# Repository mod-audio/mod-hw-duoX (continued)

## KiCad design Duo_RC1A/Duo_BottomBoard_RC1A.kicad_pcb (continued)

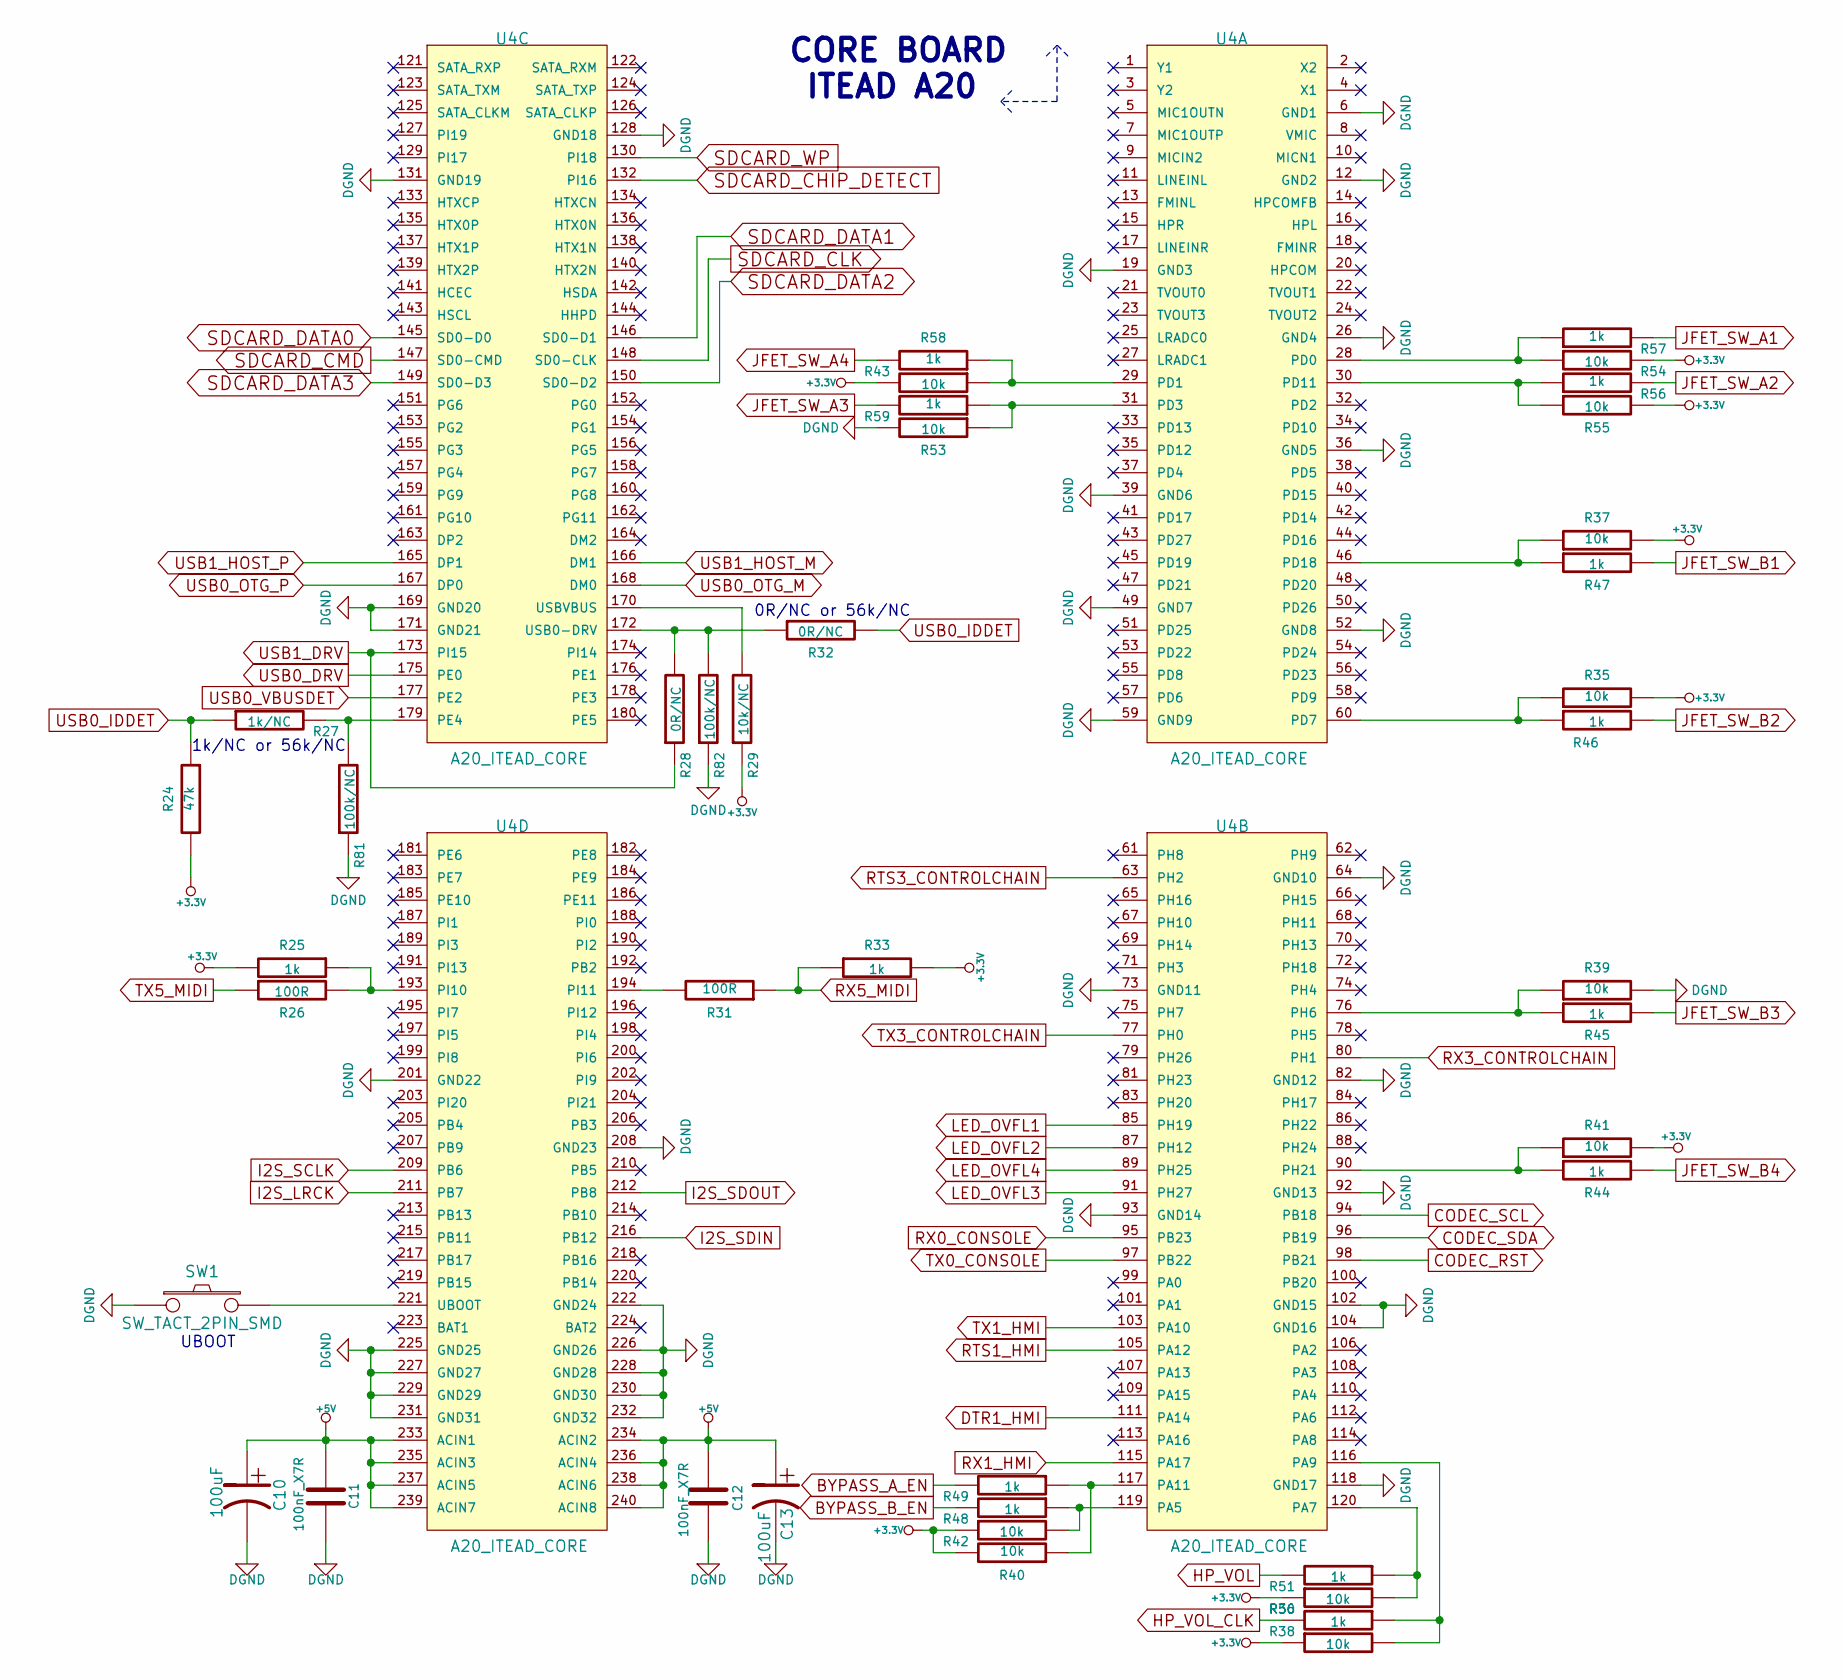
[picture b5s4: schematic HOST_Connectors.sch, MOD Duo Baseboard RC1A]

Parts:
C10, C13: 100uF; Capacitor5x11RM2
C11, C12: 100nF_X7R; SM0603
R24: 47k; SM0603
R25, R33, R44, R45, R46, R47, R48, R49, R50, R51, R56, R57, R58, R59: 1k; SM0603
R26, R31: 100R; SM0603
R27: 1k/NC; SM0603
R28, R32: 0R/NC; SM0603
R29: 10k/NC; SM0603
R35, R36, R37, R38, R39, R40, R41, R42, R43, R53, R54, R55: 10k; SM0603
R81, R82: 100k/NC; SM0603
SW1: SW_TACT_2PIN_SMD; SWITCH_SMD_FSMSM
U4: A20_ITEAD_CORE; A20_ITEAD

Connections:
+3.3V: R24.2, R25.2, R29.1, R33.2, R35.2, R36.1, R37.2, R38.1, R40.2, R41.2, R42.1, R43.2, R54.2, R55.2; also elsewhere on the board
+5V: C10.1, C11.1, C12.2, C13.1, U4.233 (ACIN1), U4.234 (ACIN2), U4.235 (ACIN3), U4.236 (ACIN4), U4.237 (ACIN5), U4.238 (ACIN6), U4.239 (ACIN7), U4.240 (ACIN8); also elsewhere on the board
BYPASS_A_EN: R49.2; also elsewhere on the board
BYPASS_B_EN: R48.2; also elsewhere on the board
CODEC_RST: U4.98 (PB21); also elsewhere on the board
CODEC_SCL: U4.94 (PB18); also elsewhere on the board
CODEC_SDA: U4.96 (PB19); also elsewhere on the board
DGND: C10.2, C11.2, C12.1, C13.2, R39.2, R53.2, R81.1, R82.1, SW1.1, U4.6 (GND1), U4.12 (GND2), U4.19 (GND3), U4.26 (GND4), U4.36 (GND5), U4.39 (GND6), U4.49 (GND7), U4.52 (GND8), U4.59 (GND9), U4.64 (GND10), U4.73 (GND11), U4.82 (GND12), U4.92 (GND13), U4.93 (GND14), U4.102 (GND15), U4.104 (GND16), U4.118 (GND17), U4.128 (GND18), U4.131 (GND19), U4.169 (GND20), U4.171 (GND21), U4.201 (GND22), U4.208 (GND23), U4.222 (GND24), U4.225 (GND25), U4.226 (GND26), U4.227 (GND27), U4.228 (GND28), U4.229 (GND29), U4.230 (GND30), U4.231 (GND31), U4.232 (GND32); also elsewhere on the board
DTR1_HMI: U4.111 (PA14); also elsewhere on the board
HP_VOL: R51.2; also elsewhere on the board
HP_VOL_CLK: R50.2; also elsewhere on the board
I2S_LRCK: U4.211 (PB7); also elsewhere on the board
I2S_SCLK: U4.209 (PB6); also elsewhere on the board
I2S_SDIN: U4.216 (PB12); also elsewhere on the board
I2S_SDOUT: U4.212 (PB8); also elsewhere on the board
JFET_SW_A1: R57.2; also elsewhere on the board
JFET_SW_A2: R56.2; also elsewhere on the board
JFET_SW_A3: R59.2; also elsewhere on the board
JFET_SW_A4: R58.2; also elsewhere on the board
JFET_SW_B1: R47.2; also elsewhere on the board
JFET_SW_B2: R46.2; also elsewhere on the board
JFET_SW_B3: R45.2; also elsewhere on the board
JFET_SW_B4: R44.2; also elsewhere on the board
LED_OVFL1: U4.85 (PH19); also elsewhere on the board
LED_OVFL2: U4.87 (PH12); also elsewhere on the board
LED_OVFL3: U4.91 (PH27); also elsewhere on the board
LED_OVFL4: U4.89 (PH25); also elsewhere on the board
unnamed: R25.1, R26.2, U4.193 (PI10)
unnamed: R27.2, R81.2, U4.179 (PE4)
unnamed: R28.2, R32.1, R82.2, U4.172 (USB0-DRV)
unnamed: R29.2, U4.170 (USBVBUS)
unnamed: R31.2, U4.194 (PI11)
unnamed: R35.1, R46.1, U4.60 (PD7)
unnamed: R36.2, R51.1, U4.120 (PA7)
unnamed: R37.1, R47.1, U4.46 (PD18)
unnamed: R38.2, R50.1, U4.116 (PA9)
unnamed: R39.1, R45.1, U4.76 (PH6)
unnamed: R40.1, R49.1, U4.117 (PA11)
unnamed: R41.1, R44.1, U4.90 (PH21)
unnamed: R42.2, R48.1, U4.119 (PA5)
unnamed: R43.1, R58.1, U4.29 (PD1)
unnamed: R53.1, R59.1, U4.31 (PD3)
unnamed: R54.1, R57.1, U4.28 (PD0)
unnamed: R55.1, R56.1, U4.30 (PD11)
unnamed: SW1.2, U4.221 (UBOOT)
RTS1_HMI: U4.105 (PA12); also elsewhere on the board
RTS3_CONTROLCHAIN: U4.63 (PH2); also elsewhere on the board
RX0_CONSOLE: U4.95 (PB23); also elsewhere on the board
RX1_HMI: U4.115 (PA17); also elsewhere on the board
RX3_CONTROLCHAIN: U4.80 (PH1); also elsewhere on the board
RX5_MIDI: R31.1, R33.1; also elsewhere on the board
SDCARD_CHIP_DETECT: U4.132 (PI16); also elsewhere on the board
SDCARD_CLK: U4.148 (SD0-CLK); also elsewhere on the board
SDCARD_CMD: U4.147 (SD0-CMD); also elsewhere on the board
SDCARD_DATA0: U4.145 (SD0-D0); also elsewhere on the board
SDCARD_DATA1: U4.146 (SD0-D1); also elsewhere on the board
SDCARD_DATA2: U4.150 (SD0-D2); also elsewhere on the board
SDCARD_DATA3: U4.149 (SD0-D3); also elsewhere on the board
SDCARD_WP: U4.130 (PI18); also elsewhere on the board
TX0_CONSOLE: U4.97 (PB22); also elsewhere on the board
TX1_HMI: U4.103 (PA10); also elsewhere on the board
TX3_CONTROLCHAIN: U4.77 (PH0); also elsewhere on the board
TX5_MIDI: R26.1; also elsewhere on the board
USB0_DRV: U4.175 (PE0); also elsewhere on the board
USB0_IDDET: R24.1, R27.1, R32.2; also elsewhere on the board
USB0_OTG_M: U4.168 (DM0); also elsewhere on the board
USB0_OTG_P: U4.167 (DP0); also elsewhere on the board
USB0_VBUSDET: U4.177 (PE2); also elsewhere on the board
USB1_DRV: R28.1, U4.173 (PI15); also elsewhere on the board
USB1_HOST_M: U4.166 (DM1); also elsewhere on the board
USB1_HOST_P: U4.165 (DP1); also elsewhere on the board

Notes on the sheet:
CORE BOARD ITEAD A20
UBOOT
0R/NC or 56k/NC
1k/NC or 56k/NC

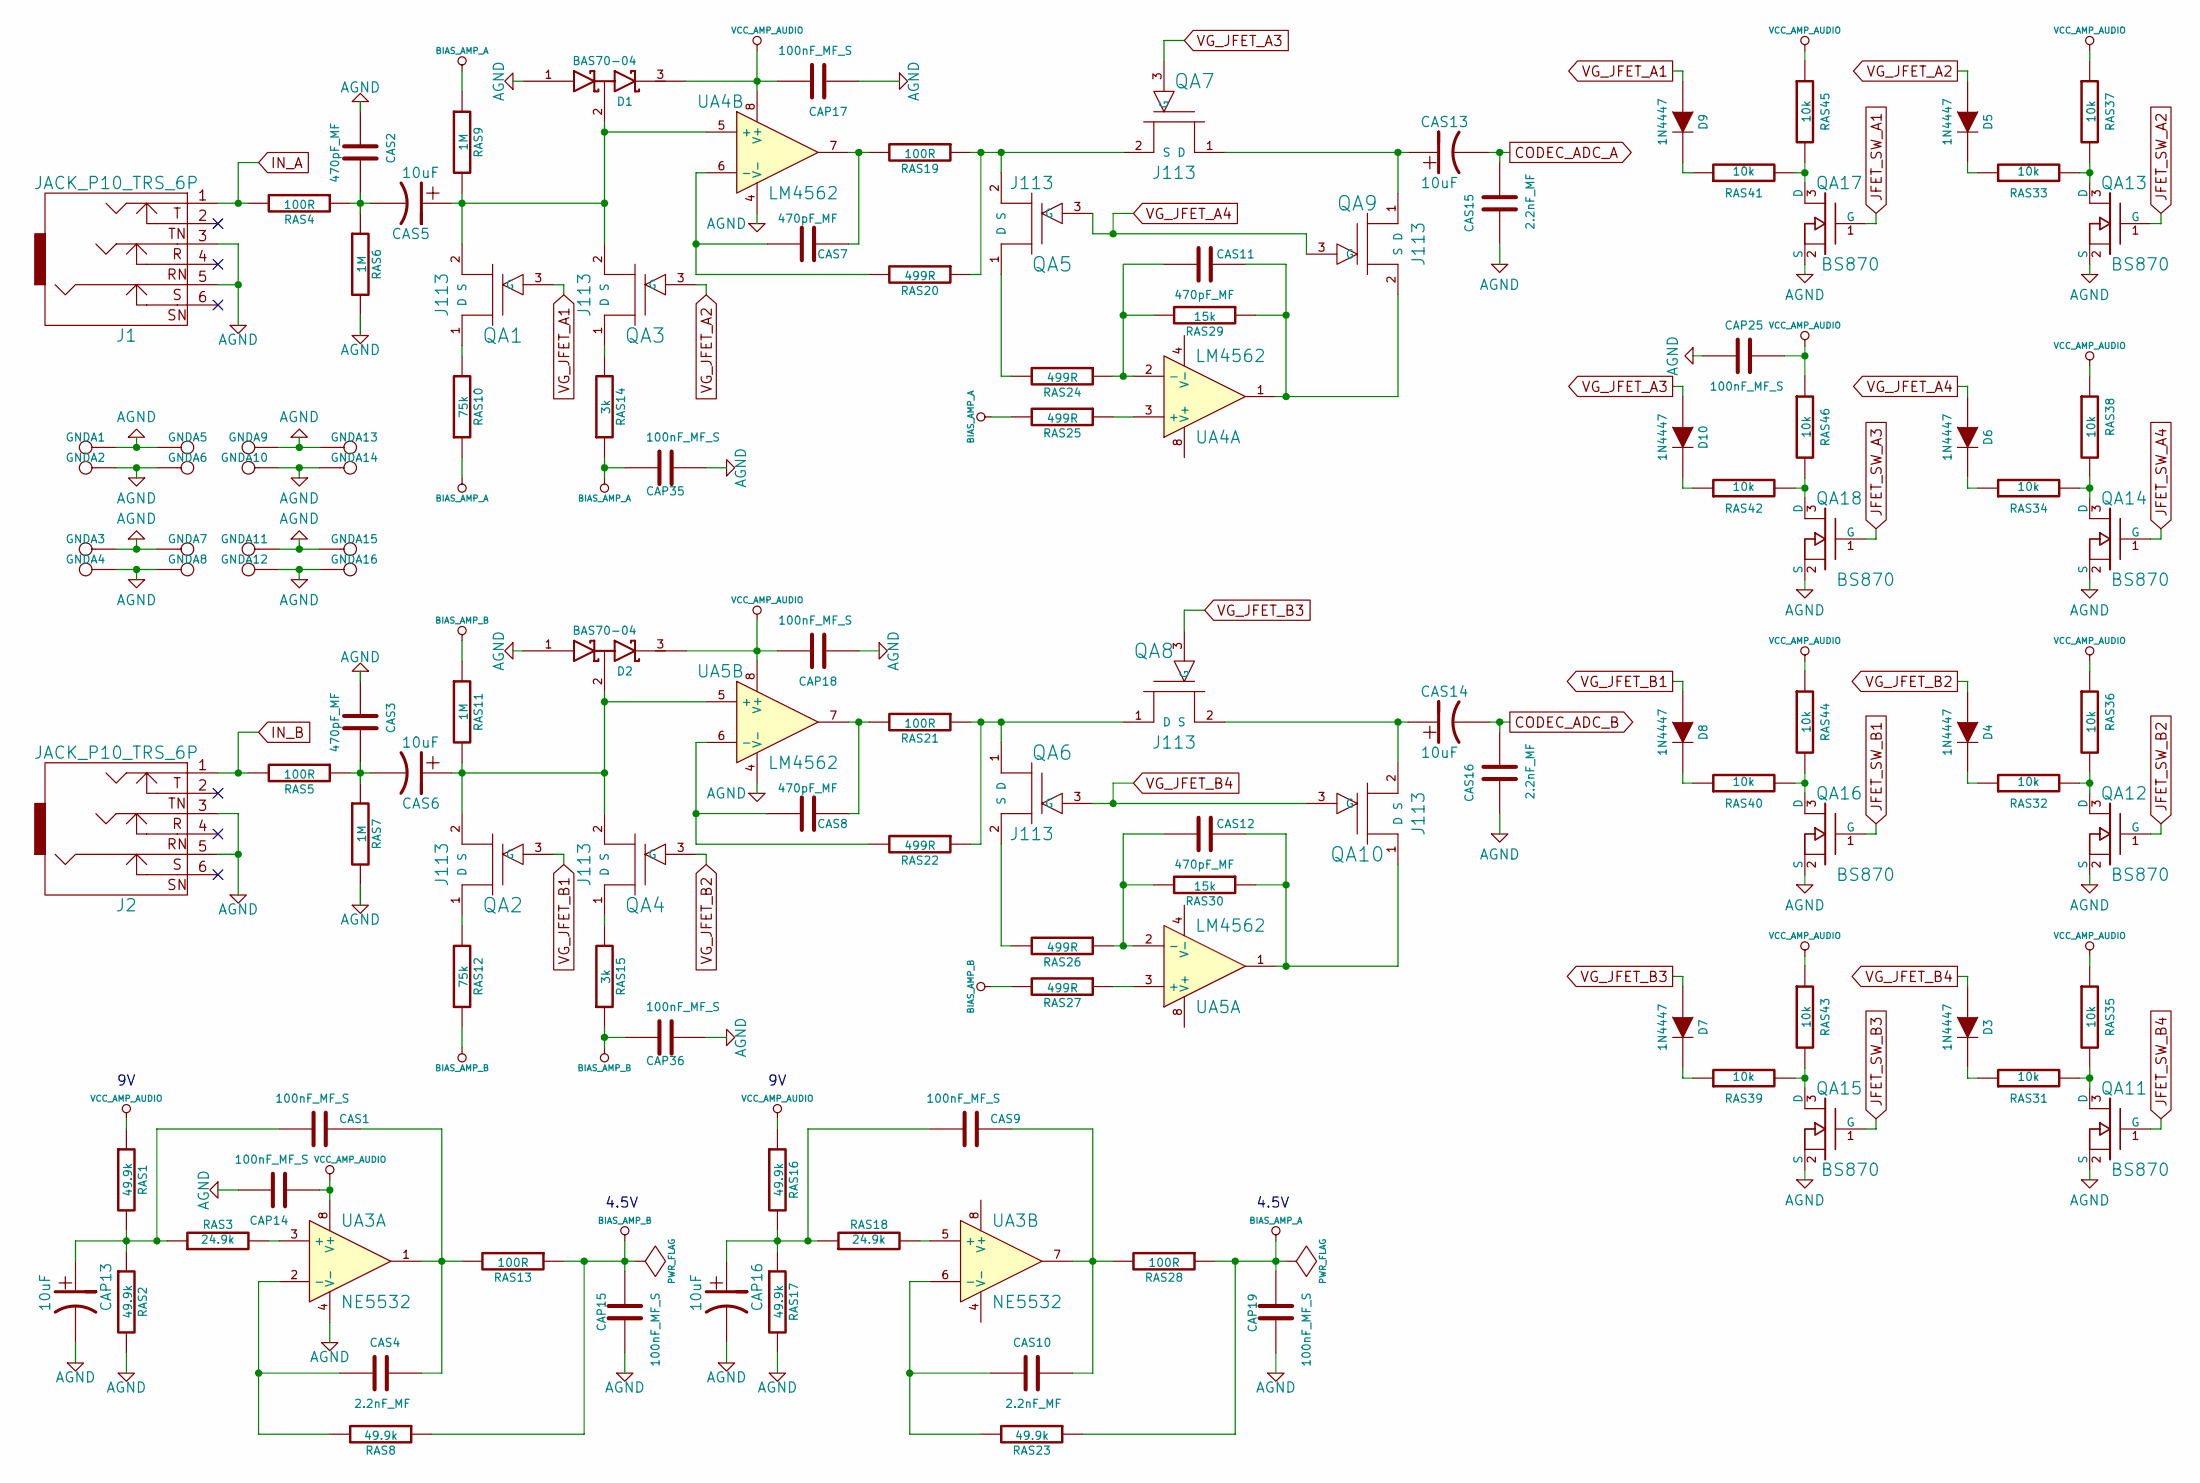
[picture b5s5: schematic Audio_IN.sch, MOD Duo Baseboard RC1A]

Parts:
CAP13, CAP16: 10uF; Capacitor5x11RM2
CAP14, CAP15, CAP17, CAP18, CAP19, CAP25, CAP35, CAP36: 100nF_MF_S; CapacitorMetalFilm_7.2x2.5MM_P5MM
CAS1, CAS9: 100nF_MF_S; CapacitorMetalFilm_7.2x2.5MM_P5MM
CAS2, CAS3, CAS7, CAS8, CAS11, CAS12: 470pF_MF; CapacitorMetalFilm_7.2x4.5MM_P5MM
CAS4, CAS10, CAS15, CAS16: 2.2nF_MF; CapacitorMetalFilm_7.2x2.5MM_P5MM
CAS5, CAS6, CAS13, CAS14: 10uF; Capacitor5x11RM2
D1, D2: BAS70-04; SOT323
D3, D4, D5, D6, D7, D8, D9, D10: 1N4447; DO-35
GNDA1, GNDA2, GNDA3, GNDA4, GNDA5, GNDA6, GNDA7, GNDA8, GNDA9, GNDA10, GNDA11, GNDA12, GNDA13, GNDA14, GNDA15, GNDA16: PAD_GND; GNDPAD_18_8MIL
J1, J2: JACK_P10_TRS_6P; JACK-NMJ6HCD2_1
QA1, QA2, QA3, QA4, QA5, QA6, QA7, QA8, QA9, QA10: J113; TO92_INLINE
QA11, QA12, QA13, QA14, QA15, QA16, QA17, QA18: BS870; SOT23
RAS1, RAS2, RAS8, RAS16, RAS17, RAS23: 49.9k; Resistor_PTH_6.35x2.35mm
RAS3, RAS18: 24.9k; Resistor_PTH_6.35x2.35mm
RAS4, RAS5, RAS13, RAS19, RAS21, RAS28: 100R; Resistor_PTH_6.35x2.35mm
RAS6, RAS7, RAS9, RAS11: 1M; Resistor_PTH_6.35x2.35mm
RAS10, RAS12: 75k; Resistor_PTH_6.35x2.35mm
RAS14, RAS15: 3k; Resistor_PTH_6.35x2.35mm
RAS20, RAS22, RAS24, RAS25, RAS26, RAS27: 499R; Resistor_PTH_6.35x2.35mm
RAS29, RAS30: 15k; Resistor_PTH_6.35x2.35mm
RAS31, RAS32, RAS33, RAS34, RAS35, RAS36, RAS37, RAS38, RAS39, RAS40, RAS41, RAS42, RAS43, RAS44, RAS45, RAS46: 10k; Resistor_PTH_6.35x2.35mm
UA3: NE5532; SOIC8_E
UA4, UA5: LM4562; SOIC8_E

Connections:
BIAS_AMP_A: CAP19.2, CAP35.2, RAS9.1, RAS10.1, RAS14.1, RAS23.1, RAS25.2, RAS28.1
BIAS_AMP_B: CAP15.2, CAP36.2, RAS8.1, RAS11.1, RAS12.1, RAS13.1, RAS15.1, RAS27.2
CODEC_ADC_A: CAS13.2, CAS15.2; also elsewhere on the board
CODEC_ADC_B: CAS14.2, CAS16.2; also elsewhere on the board
DGND: CAP13.2, CAP14.1, CAP15.1, CAP16.2, CAP17.1, CAP18.1, CAP19.1, CAP25.1, CAP35.1, CAP36.1, CAS2.2, CAS3.2, CAS15.1, CAS16.1, D1.1 (Anode), D2.1 (Anode), GNDA1.1, GNDA2.1, GNDA3.1, GNDA4.1, GNDA5.1, GNDA6.1, GNDA7.1, GNDA8.1, GNDA9.1, GNDA10.1, GNDA11.1, GNDA12.1, GNDA13.1, GNDA14.1, GNDA15.1, GNDA16.1, J1.3, J1.5, J2.3, J2.5, QA11.2 (S), QA12.2 (S), QA13.2 (S), QA14.2 (S), QA15.2 (S), QA16.2 (S), QA17.2 (S), QA18.2 (S), RAS2.2, RAS6.2, RAS7.2, RAS17.2, UA3.4 (V-), UA4.4 (V-), UA5.4 (V-); also elsewhere on the board
IN_A: J1.1, RAS4.2; also elsewhere on the board
IN_B: J2.1, RAS5.2; also elsewhere on the board
JFET_SW_A1: QA17.1 (G); also elsewhere on the board
JFET_SW_A2: QA13.1 (G); also elsewhere on the board
JFET_SW_A3: QA18.1 (G); also elsewhere on the board
JFET_SW_A4: QA14.1 (G); also elsewhere on the board
JFET_SW_B1: QA16.1 (G); also elsewhere on the board
JFET_SW_B2: QA12.1 (G); also elsewhere on the board
JFET_SW_B3: QA15.1 (G); also elsewhere on the board
JFET_SW_B4: QA11.1 (G); also elsewhere on the board
unnamed: CAP13.1, CAS1.1, RAS1.2, RAS2.1, RAS3.1
unnamed: CAP16.1, CAS9.1, RAS16.2, RAS17.1, RAS18.1
unnamed: CAS1.2, CAS4.2, RAS13.2, UA3.1
unnamed: CAS2.1, CAS5.2, RAS4.1, RAS6.1
unnamed: CAS3.1, CAS6.2, RAS5.1, RAS7.1
unnamed: CAS4.1, RAS8.2, UA3.2 (-)
unnamed: CAS5.1, D1.2 (AK), QA1.2 (S), QA3.2 (S), RAS9.2, UA4.5 (+)
unnamed: CAS6.1, D2.2 (AK), QA2.2 (S), QA4.2 (S), RAS11.2, UA5.5 (+)
unnamed: CAS7.1, RAS20.2, UA4.6 (-)
unnamed: CAS7.2, RAS19.2, UA4.7
unnamed: CAS8.1, RAS22.2, UA5.6 (-)
unnamed: CAS8.2, RAS21.2, UA5.7
unnamed: CAS10.1, RAS23.2, UA3.6 (-)
unnamed: CAS9.2, CAS10.2, RAS28.2, UA3.7
unnamed: CAS11.1, RAS24.1, RAS29.2, UA4.2 (-)
unnamed: CAS11.2, QA9.2 (S), RAS29.1, UA4.1
unnamed: CAS12.1, RAS26.1, RAS30.2, UA5.2 (-)
unnamed: CAS12.2, QA10.1 (D), RAS30.1, UA5.1
unnamed: CAS13.1, QA7.1 (D), QA9.1 (D)
unnamed: CAS14.1, QA8.2 (S), QA10.2 (S)
unnamed: D3.2 (K), RAS31.1
unnamed: D4.2 (K), RAS32.1
unnamed: D5.2 (K), RAS33.1
unnamed: D6.2 (K), RAS34.1
unnamed: D7.2 (K), RAS39.1
unnamed: D8.2 (K), RAS40.1
unnamed: D9.2 (K), RAS41.1
unnamed: D10.2 (K), RAS42.1
unnamed: QA1.1 (D), RAS10.2
unnamed: QA2.1 (D), RAS12.2
unnamed: QA3.1 (D), RAS14.2
unnamed: QA4.1 (D), RAS15.2
unnamed: QA5.1 (D), RAS24.2
unnamed: QA5.2 (S), QA7.2 (S), RAS19.1, RAS20.1
unnamed: QA6.1 (D), QA8.1 (D), RAS21.1, RAS22.1
unnamed: QA6.2 (S), RAS26.2
unnamed: QA11.3 (D), RAS31.2, RAS35.2
unnamed: QA12.3 (D), RAS32.2, RAS36.2
unnamed: QA13.3 (D), RAS33.2, RAS37.2
unnamed: QA14.3 (D), RAS34.2, RAS38.2
unnamed: QA15.3 (D), RAS39.2, RAS43.2
unnamed: QA16.3 (D), RAS40.2, RAS44.2
unnamed: QA17.3 (D), RAS41.2, RAS45.2
unnamed: QA18.3 (D), RAS42.2, RAS46.2
unnamed: RAS3.2, UA3.3 (+)
unnamed: RAS18.2, UA3.5 (+)
unnamed: RAS25.1, UA4.3 (+)
unnamed: RAS27.1, UA5.3 (+)
VCC_AMP_AUDIO: CAP14.2, CAP17.2, CAP18.2, CAP25.2, D1.3 (cathode), D2.3 (cathode), RAS1.1, RAS16.1, RAS35.1, RAS36.1, RAS37.1, RAS38.1, RAS43.1, RAS44.1, RAS45.1, RAS46.1, UA3.8 (V+), UA4.8 (V+), UA5.8 (V+); also elsewhere on the board
VG_JFET_A1: D9.1 (A), QA1.3 (G)
VG_JFET_A2: D5.1 (A), QA3.3 (G)
VG_JFET_A3: D10.1 (A), QA7.3 (G)
VG_JFET_A4: D6.1 (A), QA5.3 (G), QA9.3 (G)
VG_JFET_B1: D8.1 (A), QA2.3 (G)
VG_JFET_B2: D4.1 (A), QA4.3 (G)
VG_JFET_B3: D7.1 (A), QA8.3 (G)
VG_JFET_B4: D3.1 (A), QA6.3 (G), QA10.3 (G)

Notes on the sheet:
4.5V

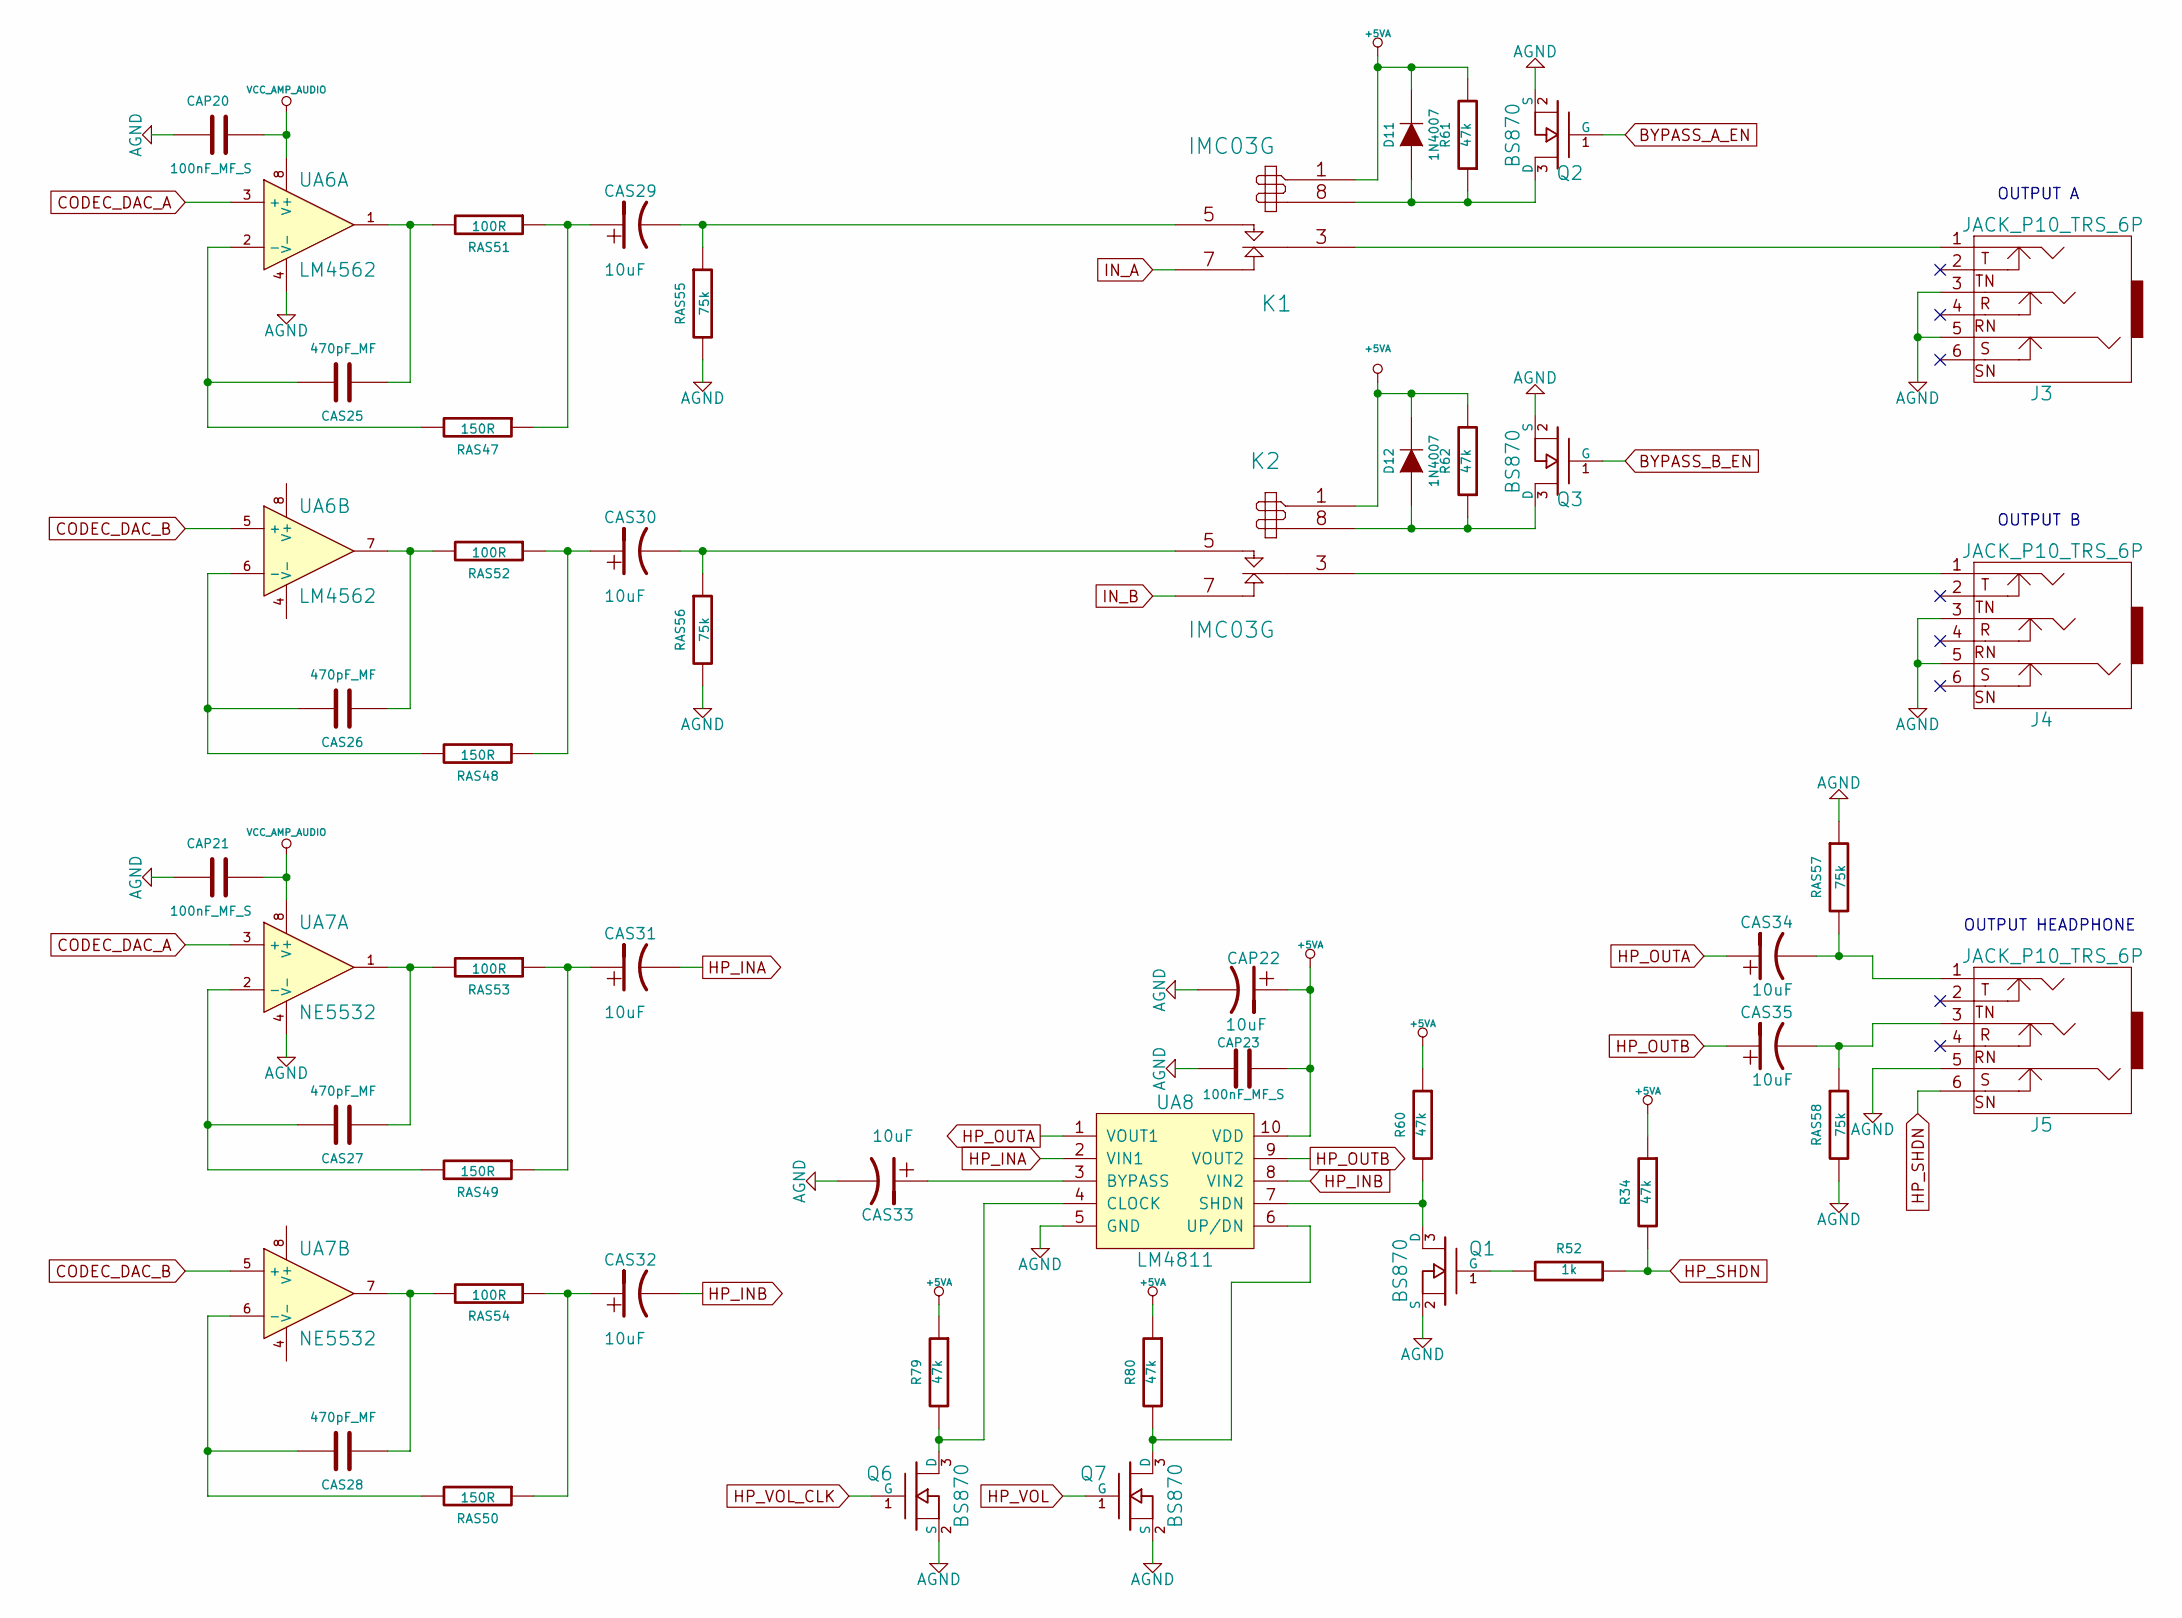
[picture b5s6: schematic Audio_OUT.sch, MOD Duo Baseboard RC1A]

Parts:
CAP20, CAP21, CAP23: 100nF_MF_S; CapacitorMetalFilm_7.2x2.5MM_P5MM
CAP22: 10uF; Capacitor5x11RM2
CAS25, CAS26, CAS27, CAS28: 470pF_MF; CapacitorMetalFilm_7.2x4.5MM_P5MM
CAS29, CAS30, CAS31, CAS32, CAS33, CAS34, CAS35: 10uF; Capacitor5x11RM2
D11, D12: 1N4007; DO-214AC(SMA)
J3, J4, J5: JACK_P10_TRS_6P; JACK-NMJ6HCD2_1
K1, K2: IMC03G
Q1, Q2, Q3, Q6, Q7: BS870; SOT23
R34, R60, R61, R62, R79, R80: 47k; SM0603
R52: 1k; SM0603
RAS47, RAS48, RAS49, RAS50: 150R; Resistor_PTH_6.35x2.35mm
RAS51, RAS52, RAS53, RAS54: 100R; Resistor_PTH_6.35x2.35mm
RAS55, RAS56, RAS57, RAS58: 75k; Resistor_PTH_6.35x2.35mm
UA6: LM4562; SOIC8_E
UA7: NE5532; SOIC8_E
UA8: LM4811; MSOP10

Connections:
+5VA: CAP22.1, CAP23.2, D11.2 (K), D12.2 (K), K1.1, K2.1, R34.1, R60.1, R61.2, R62.2, R79.1, R80.1, UA8.10 (VDD); also elsewhere on the board
BYPASS_A_EN: Q2.1 (G); also elsewhere on the board
BYPASS_B_EN: Q3.1 (G); also elsewhere on the board
CODEC_DAC_A: UA6.3 (+), UA7.3 (+); also elsewhere on the board
CODEC_DAC_B: UA6.5 (+), UA7.5 (+); also elsewhere on the board
DGND: CAP20.1, CAP21.1, CAP22.2, CAP23.1, CAS33.2, J3.3, J3.5, J4.3, J4.5, J5.5, Q1.2 (S), Q2.2 (S), Q3.2 (S), Q6.2 (S), Q7.2 (S), RAS55.2, RAS56.2, RAS57.1, RAS58.2, UA6.4 (V-), UA7.4 (V-), UA8.5 (GND); also elsewhere on the board
HP_INA: CAS31.2, UA8.2 (VIN1)
HP_INB: CAS32.2, UA8.8 (VIN2)
HP_OUTA: CAS34.1, UA8.1 (VOUT1)
HP_OUTB: CAS35.1, UA8.9 (VOUT2)
HP_SHDN: J5.6, R34.2, R52.1
HP_VOL: Q7.1 (G); also elsewhere on the board
HP_VOL_CLK: Q6.1 (G); also elsewhere on the board
IN_A: K1.7 (R); also elsewhere on the board
IN_B: K2.7 (R); also elsewhere on the board
unnamed: CAS25.1, RAS51.2, UA6.1
unnamed: CAS25.2, RAS47.2, UA6.2 (-)
unnamed: CAS26.1, RAS52.2, UA6.7
unnamed: CAS26.2, RAS48.2, UA6.6 (-)
unnamed: CAS27.1, RAS53.2, UA7.1
unnamed: CAS27.2, RAS49.2, UA7.2 (-)
unnamed: CAS28.1, RAS54.2, UA7.7
unnamed: CAS28.2, RAS50.2, UA7.6 (-)
unnamed: CAS29.1, RAS47.1, RAS51.1
unnamed: CAS29.2, K1.5 (T), RAS55.1
unnamed: CAS30.1, RAS48.1, RAS52.1
unnamed: CAS30.2, K2.5 (T), RAS56.1
unnamed: CAS31.1, RAS49.1, RAS53.1
unnamed: CAS32.1, RAS50.1, RAS54.1
unnamed: CAS33.1, UA8.3 (BYPASS)
unnamed: CAS34.2, J5.1, RAS57.2
unnamed: CAS35.2, J5.3, RAS58.1
unnamed: D11.1 (A), K1.8, Q2.3 (D), R61.1
unnamed: D12.1 (A), K2.8, Q3.3 (D), R62.1
unnamed: J3.1, K1.3 (C)
unnamed: J4.1, K2.3 (C)
unnamed: Q1.1 (G), R52.2
unnamed: Q1.3 (D), R60.2, UA8.7 (SHDN)
unnamed: Q6.3 (D), R79.2, UA8.4 (CLOCK)
unnamed: Q7.3 (D), R80.2, UA8.6 (UP/DN)
VCC_AMP_AUDIO: CAP20.2, CAP21.2, UA6.8 (V+), UA7.8 (V+); also elsewhere on the board

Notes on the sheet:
OUTPUT A
OUTPUT B
OUTPUT HEADPHONE

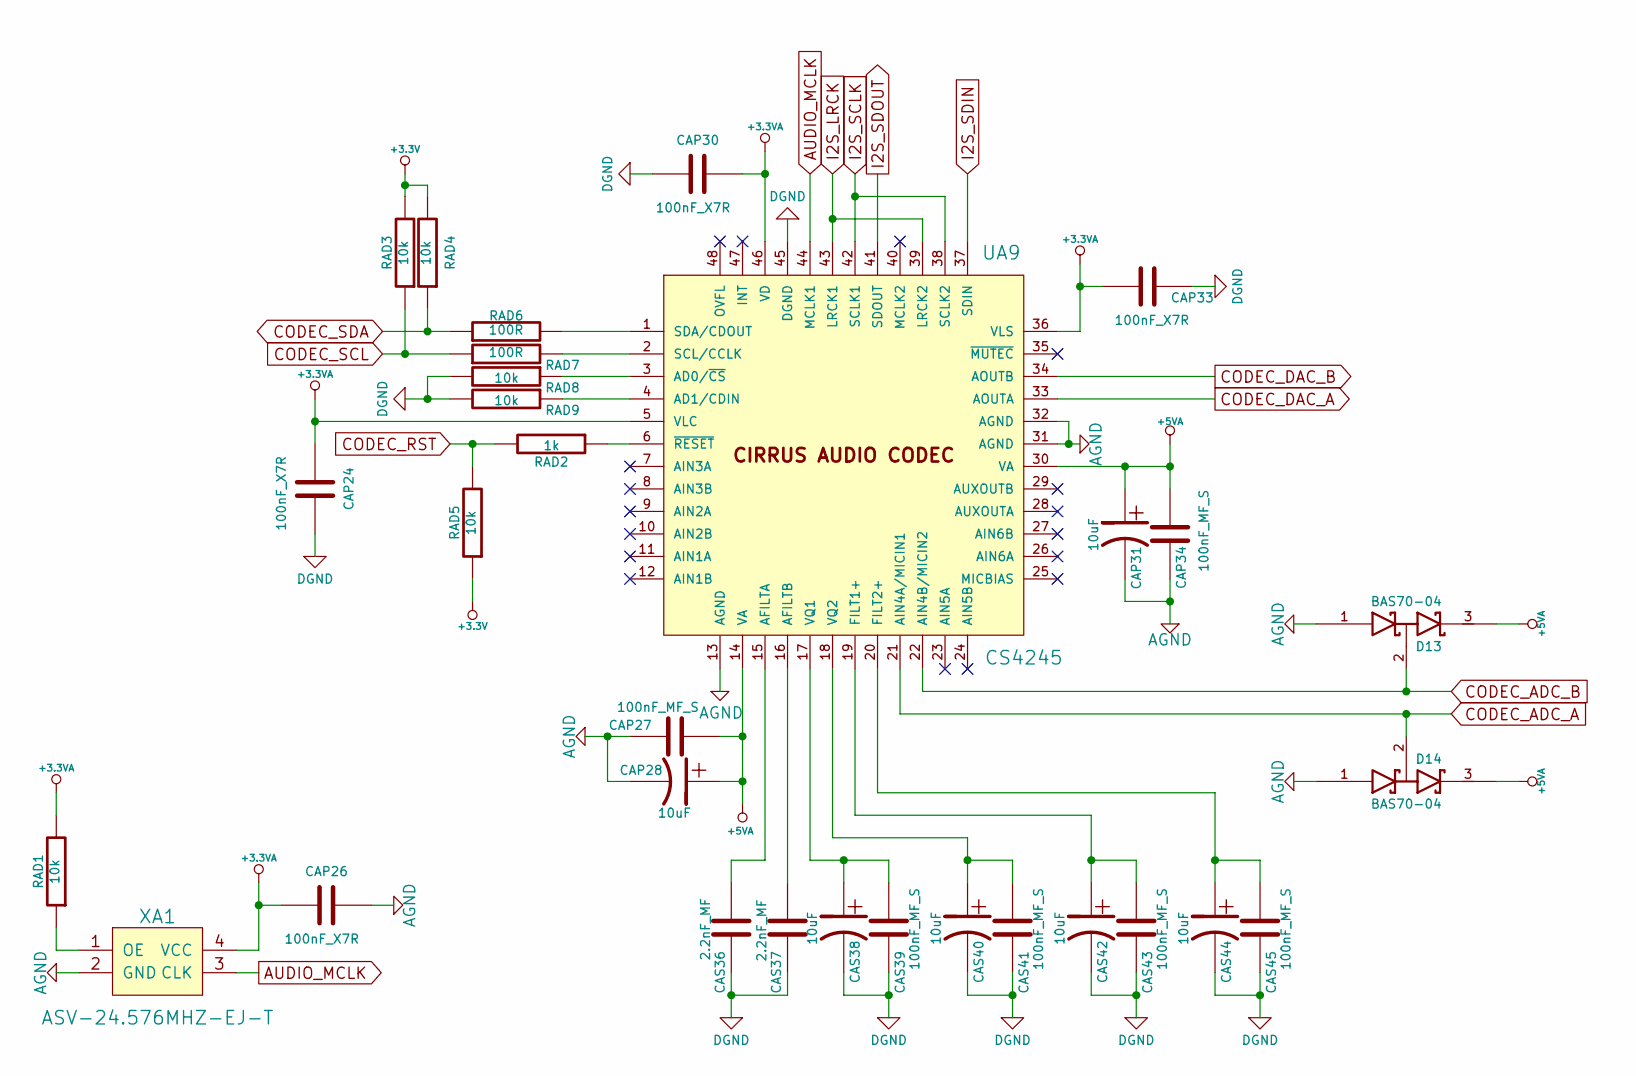
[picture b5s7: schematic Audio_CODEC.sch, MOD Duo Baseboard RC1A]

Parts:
CAP24, CAP26, CAP30, CAP33: 100nF_X7R; SM0603
CAP27, CAP34: 100nF_MF_S; CapacitorMetalFilm_7.2x2.5MM_P5MM
CAP28, CAP31: 10uF; Capacitor5x11RM2
CAS36, CAS37: 2.2nF_MF; CapacitorMetalFilm_7.2x2.5MM_P5MM
CAS38, CAS40, CAS42, CAS44: 10uF; Capacitor5x11RM2
CAS39, CAS41, CAS43, CAS45: 100nF_MF_S; CapacitorMetalFilm_7.2x2.5MM_P5MM
D13, D14: BAS70-04; SOT323
RAD1, RAD3, RAD4, RAD5, RAD8, RAD9: 10k; SM0603
RAD2: 1k; SM0603
RAD6, RAD7: 100R; SM0603
UA9: CS4245; LQFP48
XA1: ASV-24.576MHZ-EJ-T; SMD4_DFN

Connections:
+3.3V: RAD3.2, RAD4.2, RAD5.1; also elsewhere on the board
+3.3VA: CAP24.2, CAP26.1, CAP30.2, CAP33.2, RAD1.2, UA9.5 (VLC), UA9.36 (VLS), UA9.46 (VD), XA1.4 (VCC); also elsewhere on the board
+5VA: CAP27.2, CAP28.1, CAP31.1, CAP34.2, D13.3 (cathode), D14.3 (cathode), UA9.14 (VA), UA9.30 (VA); also elsewhere on the board
AUDIO_MCLK: UA9.44 (MCLK1), XA1.3 (CLK)
CODEC_ADC_A: D14.2 (AK), UA9.21 (AIN4A/MICIN1); also elsewhere on the board
CODEC_ADC_B: D13.2 (AK), UA9.22 (AIN4B/MICIN2); also elsewhere on the board
CODEC_DAC_A: UA9.33 (AOUTA); also elsewhere on the board
CODEC_DAC_B: UA9.34 (AOUTB); also elsewhere on the board
CODEC_RST: RAD2.2, RAD5.2; also elsewhere on the board
CODEC_SCL: RAD3.1, RAD7.1; also elsewhere on the board
CODEC_SDA: RAD4.1, RAD6.1; also elsewhere on the board
DGND: CAP24.1, CAP26.2, CAP27.1, CAP28.2, CAP30.1, CAP31.2, CAP33.1, CAP34.1, CAS36.1, CAS37.1, CAS38.2, CAS39.1, CAS40.2, CAS41.1, CAS42.2, CAS43.1, CAS44.2, CAS45.1, D13.1 (Anode), D14.1 (Anode), RAD8.2, RAD9.2, UA9.13 (AGND), UA9.31 (AGND), UA9.32 (AGND), UA9.45 (DGND), XA1.2 (GND); also elsewhere on the board
I2S_LRCK: UA9.39 (LRCK2), UA9.43 (LRCK1); also elsewhere on the board
I2S_SCLK: UA9.38 (SCLK2), UA9.42 (SCLK1); also elsewhere on the board
I2S_SDIN: UA9.37 (SDIN); also elsewhere on the board
I2S_SDOUT: UA9.41 (SDOUT); also elsewhere on the board
unnamed: CAS36.2, UA9.15 (AFILTA)
unnamed: CAS37.2, UA9.16 (AFILTB)
unnamed: CAS38.1, CAS39.2, UA9.17 (VQ1)
unnamed: CAS40.1, CAS41.2, UA9.18 (VQ2)
unnamed: CAS42.1, CAS43.2, UA9.19 (FILT1+)
unnamed: CAS44.1, CAS45.2, UA9.20 (FILT2+)
unnamed: RAD1.1, XA1.1 (OE)
unnamed: RAD2.1, UA9.6 (~RESET)
unnamed: RAD6.2, UA9.1 (SDA/CDOUT)
unnamed: RAD7.2, UA9.2 (SCL/CCLK)
unnamed: RAD8.1, UA9.3 (AD0/~CS)
unnamed: RAD9.1, UA9.4 (AD1/CDIN)
